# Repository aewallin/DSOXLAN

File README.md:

DSOXLAN
=======

This is a simple Ethernet interface-card for Agilent/Keysight
DSO-X 2000 and 3000 series oscilloscopes. The original Agilent/Keysight 
DSOXLAN module (about 326 euros + VAT as of December 2014)
also includes VGA output, while this simple card provides only LAN.

Many thanks to "georges80" on the EEVBlog forum
for the original schematic and PCB layout.

Components:
* Ethernet jack, WÜRTH 7499010121A
* 2pcs 470R 0805 resistor
* 1pcs 10R 0805 resistor
* 1pcs 1n 0805 capacitor

Files:
* Kicad: schematic, PCB, project, cmp, netlist
* non-standard footprints in /footprints: Ethernet magjack, 2x40-pin card-edge connector.

3D print components for case obtained from

https://www.eevblog.com/forum/projects/diy-dsoxlan-interface-for-keysight-oscilloscopes/msg4323214/#msg4323214

The mounting holes for the screws are 3.2 mm in diameter, so M3 screws
fit well.

Apparently they have been authored by Jay_Diddy_B.

Released under the CERN OHL. See http://ohwr.org/cernohl

Images
======

Using the 3D printed front cover and spacers, the entire module looks like:

The oscilloscope features a built-in HTTP server.
The LAN settings page from the oscilloscope:

There are also options for remote control straight from the HTTP
server. Some of them require Java, but when selecting the "Tablet"
mode, it offers an HTML5 control option:

(Note: the above module has been built using a slightly different version
of the Würth RJ45 jack, 7499011121A. If anyone wants to use exactly
these, see https://github.com/dl8dtl/DSOXLAN/tree/WE7499011121A )

Links
=====
* https://web.archive.org/web/20200225205940/http://anagram.net/nuts/DSOXLAN/
* http://www.anderswallin.net/2014/12/diy-dsoxlan/

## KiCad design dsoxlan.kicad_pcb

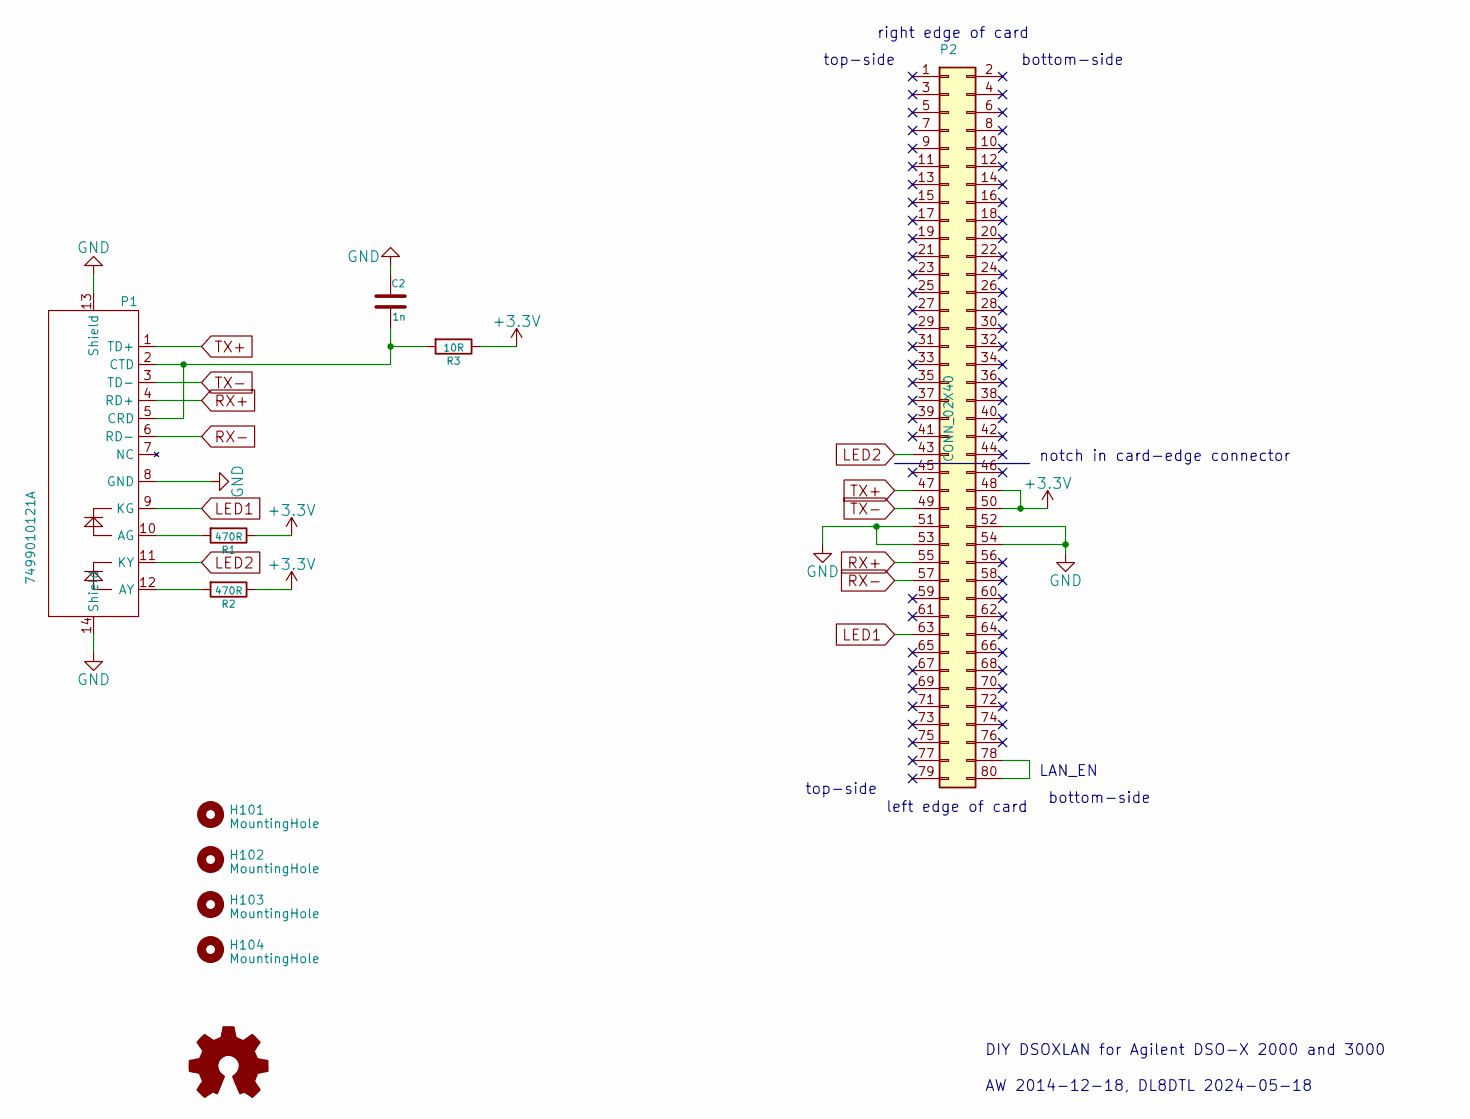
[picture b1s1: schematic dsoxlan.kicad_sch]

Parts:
C2: 1n; C_0805_2012Metric_Pad1.18x1.45mm_HandSolder
H101, H102, H103, H104: MountingHole; MountingHole_3.2mm_M3_ISO7380
P1: 7499010121A; WURTH-7499010121A
P2: CONN_02X40; cardedge_40x2
R1, R2: 470R; R_0805_2012Metric_Pad1.20x1.40mm_HandSolder
R3: 10R; R_0805_2012Metric_Pad1.20x1.40mm_HandSolder
SYM101: Logo_Open_Hardware_Small; OSHW-Symbol_6.7x6mm_Copper

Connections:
+3.3V: P2.48, P2.50, R1.1, R2.1, R3.1
GND: C2.1, P1.8 (GND), P1.13 (Shield), P1.14 (Shield), P2.51, P2.52, P2.53, P2.54
LED1: P1.9 (KG), P2.63
LED2: P1.11 (KY), P2.43
unnamed: P1.10 (AG), R1.2
unnamed: P1.12 (AY), R2.2
unnamed: C2.2, P1.2 (CTD), P1.5 (CRD), R3.2
unnamed: P2.78, P2.80
RX+: P1.4 (RD+), P2.55
RX-: P1.6 (RD-), P2.57
TX+: P1.1 (TD+), P2.47
TX-: P1.3 (TD-), P2.49

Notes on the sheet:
bottom-side
top-side
left edge of card
DIY DSOXLAN for Agilent DSO-X 2000 and 3000
AW 2014-12-18, DL8DTL 2024-05-18
right edge of card
notch in card-edge connector
LAN_EN

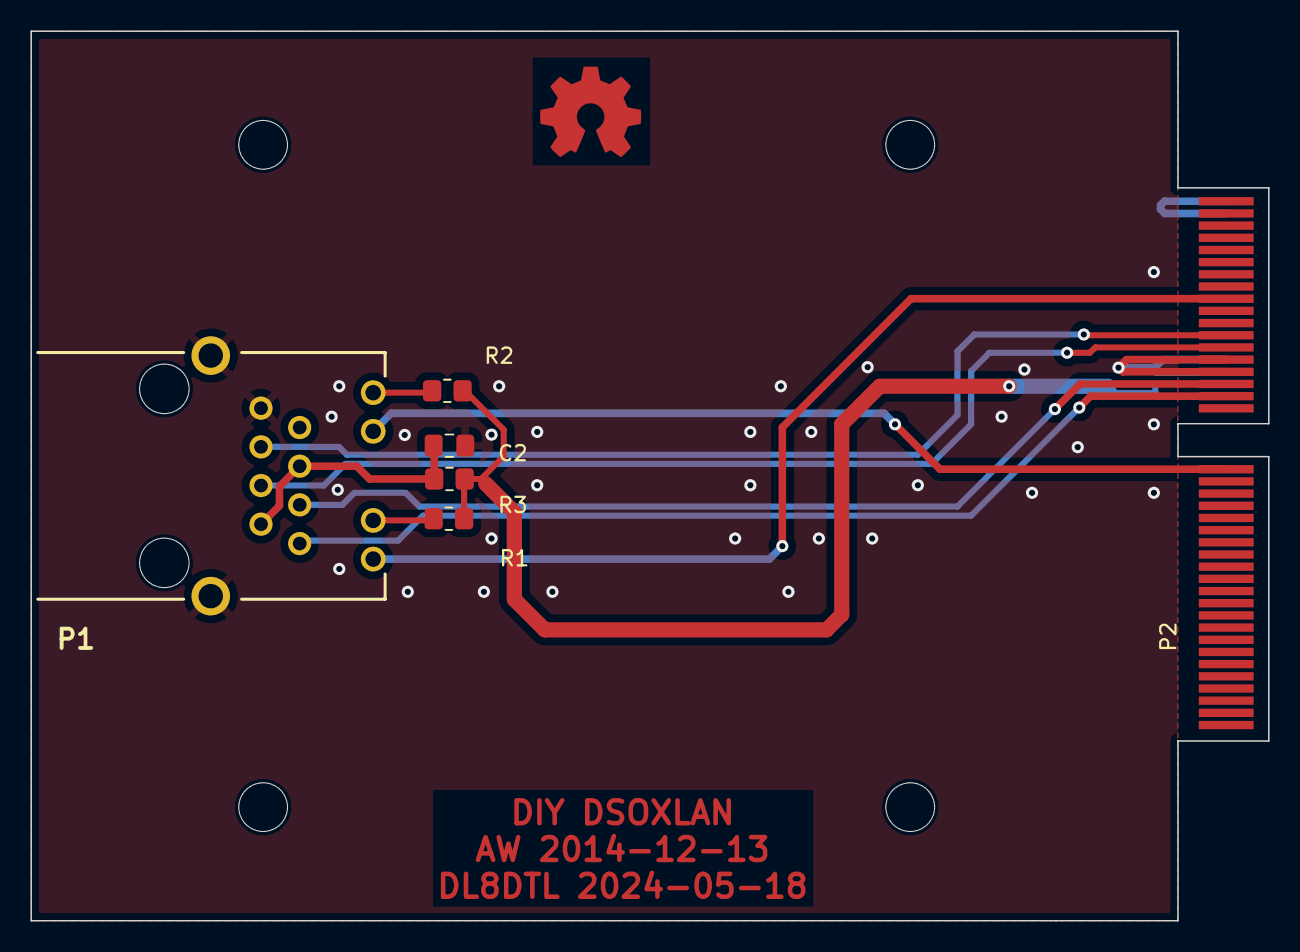
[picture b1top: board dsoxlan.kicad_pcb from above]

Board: 2 copper layers, 81.3 x 58.4 mm, 11 parts (0 on the bottom side), 12 nets.

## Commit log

2014-12-18 footprints for magjack and card-edge-connector
2014-12-18 gerbers and drill-file
2014-12-18 initial commit of kicad sources and pdf/jpg/png images/output
2014-12-18 schematic in pdf format
2014-12-18 initial text for readme
2015-12-28 add links
2018-11-04 add alternative magjack
2024-05-17 First upgrade step: fix schematic
    Create new symbol for ethernet jack, previous one was not
    migrated.
    Fix library names for remaining parts.
    Rename all project files to their new .kicad_* suffix.
2024-05-18 Basic upgrade to Kicad 7+
    Symbols had to be recreated because they were not part of
    original dataset.
    Footprint library now needs to end in .pretty
    Still many DRC warnings, but the basic result ought to be
    the same as before now.
2024-05-18 DRC fixup: remove silkscreen from outside board area
2024-05-18 Update PCB with updated components
2024-05-18 More silkscreen removal
    Move comment line into "User Comments" layer
2024-05-18 More silkscreen removal
    No point in trying to print silkscreen over a hole
2024-05-18 DRC fixup: define courtyards
2024-05-18 DSC fixup
    Replace all objects by new ones from the current libraries
    shipped by Kicad.
    This causes a slightly different OSHW (Opensource Hardware)
    logo to be used in the PCB.
    To maintain schematic parity, all mechanical objects on the
    PCB (mounting holes and OSHW logo) have their schematic
2024-05-18 Recreate Gerber files
    This now also includes Gerber files used for production at
    commercial PCB facilities:
    * solder masks
    * front silkscreen
    Drill files have been separated into PTH and NPTH files.
2024-05-18 Add symbol for Bel Fuse 08B0-1X1T-36-F
2024-05-18 Add footprint for Bel Fuse 08B0-1X1T-36-F
    Footprint obtained from Samacsys, but taken with changes:
    * mounting holes instead of pins 11/12
    * add courtyard
    * restrict silkscreen to inner area
2024-05-18 Replace RJ45 jack by Bel Fuse 08B0-1X1T-36-F
    The old TE Connectivity device is no longer available.
    Found another one that contains similar magnetics and
    termination as the TE one.
2024-05-18 Move C2 silkscreen text out of the way
2024-05-18 Regenerate Gerbers
2024-05-18 Add STP 3D model for Bel Fuse RJ45 jack
2024-05-18 Remove silkscreen prints for mounting holes
2024-05-18 Remove soldermask from OSHW logo and text at bottom
2024-05-19 Remove solder mask from edge connector
2024-05-20 Replace RJ45 jack by Würth 7499010121A
    This one appears to be readily available at various distributors.
    Also add 3D print models for case parts, obtained from
    https://www.eevblog.com/forum/projects/diy-dsoxlan-interface-for-keysight-oscilloscopes/msg4323214/#msg4323214
    apparently authored by Jay_Diddy_B.
    Adapted layout to fit these models.
2024-05-20 Update Gerber and Excellon files
2024-05-20 Remove some useless silkscreen texts from mechanical parts
2024-05-21 open with kicad8
2024-06-14 Add some images to README.md
    Two photos of the complete module, and two screenshots from
    using it.
2024-06-14 Add a hint about the 7499011121A RJ45 jack
2024-08-25 Add a LICENSE.txt file
    The file is a copy of the CERN-OHL-P v2. Adding it to the tree
    is basically required by the license itself, as it ought to be
    bundled with the files released under it.
    While being here, I have also been asked to comment on the screws
    used, so added a sentence about them.
    Also added the *-lib-table files since they describe the
2025-06-30 Update Readme.md BOM to match schematic/PCB values
2025-07-01 Add STL files for easier 3D printing - By Jay_Diddy_BTopic on EEVBlog - https://www.eevblog.com/forum/projects/diy-dsoxlan-interface-for-keysight-oscilloscopes/msg4994941/#msg4994941
2025-11-16 update to kicad9
2025-11-16 fp-lib-table and sym-lib-table not needed anymore?
2025-11-29 remove unused files
